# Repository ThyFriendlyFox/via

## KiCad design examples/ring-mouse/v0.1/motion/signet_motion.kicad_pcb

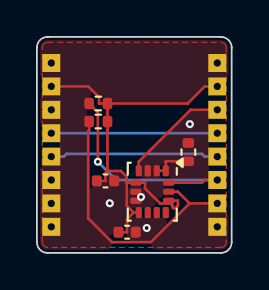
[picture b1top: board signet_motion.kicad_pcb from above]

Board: 2 copper layers, 10.8 x 12.0 mm, 8 parts (0 on the bottom side), 8 nets.

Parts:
C1, C2: 100n; C_0402_1005Metric
J1: POWER; Joint_Edge_1x08_P1.3mm
J2: RADIO; Joint_Edge_1x08_P1.3mm
R1, R2: 4.7k; R_0402_1005Metric
R3: 10k; R_0402_1005Metric
U1: LSM6DSL; LGA-14_3x2.5mm_P0.5mm_LayoutBorder3x4y

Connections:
+3V3: C1.1, C2.1, J1.2, J2.2, R1.2, R2.2, U1.5, U1.8, U1.12
/CHG_STAT: J1.5, J2.5
/I2C_SCL: J2.7, R1.1, U1.13
/I2C_SDA: J2.6, R2.1, U1.14
/IMU_INT: J2.3, U1.4
/IMU_SA0: R3.1, U1.1, U1.2
/VBAT_SENSE: J1.4, J2.4
GND: C1.2, C2.2, J1.1, J1.3, J1.6, J1.7, J1.8, J2.1, J2.8, R3.2, U1.3, U1.6, U1.7

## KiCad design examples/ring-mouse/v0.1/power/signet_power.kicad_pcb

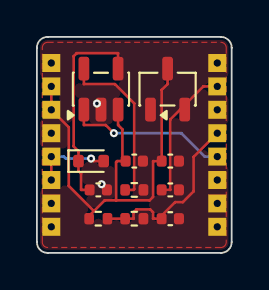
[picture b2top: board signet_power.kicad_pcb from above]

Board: 2 copper layers, 10.8 x 12.0 mm, 13 parts (0 on the bottom side), 8 nets.

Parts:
C1, C2: 4.7u; C_0402_1005Metric
C3, C4: 1u; C_0402_1005Metric
C5: 100n; C_0402_1005Metric
D2: BAT54XV2; D_SOD-523
J1: CELL; Joint_Edge_1x08_P1.3mm
J2: MOTION; Joint_Edge_1x08_P1.3mm
R1: 33k; R_0402_1005Metric
R2, R3: 1M; R_0402_1005Metric
U1: MCP73831; SOT-23-5
U2: TPS7A0533; SOT-23-3

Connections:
+3V3: C4.1, J2.2, U2.2
/CHG_STAT: J2.5, U1.1
/PROG: R1.1, U1.5
/VBAT_SENSE: C5.1, J2.4, R2.2, R3.1
GND: C1.2, C2.2, C3.2, C4.2, C5.2, J1.1, J1.4, J1.7, J1.8, J2.1, J2.3, J2.6, J2.7, J2.8, R1.2, R3.2, U1.2, U2.1
VBAT: C2.1, C3.1, J1.2, J1.3, R2.1, U1.3, U2.3
VCHG: D2.2, J1.5, J1.6
VIN_CHG: C1.1, D2.1, U1.4

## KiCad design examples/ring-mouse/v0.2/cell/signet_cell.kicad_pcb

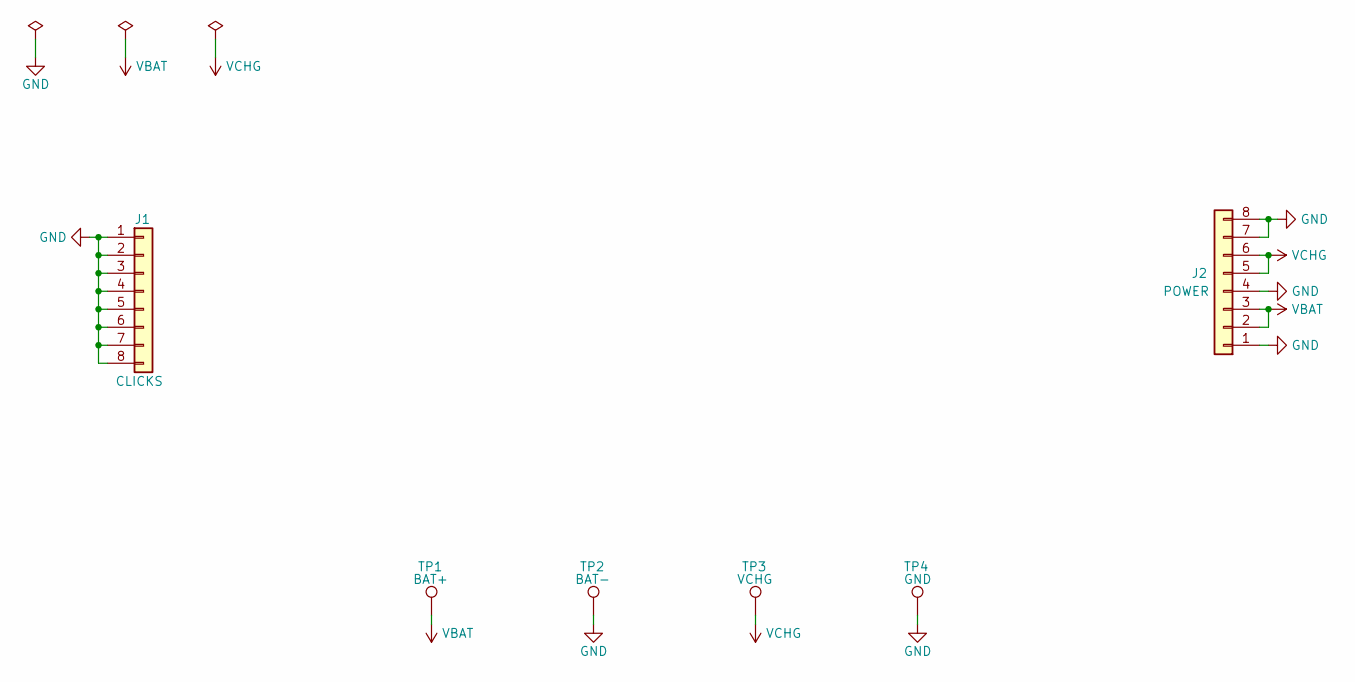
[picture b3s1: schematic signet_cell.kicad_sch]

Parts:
J1: CLICKS; Joint_Edge_1x08_P1.3mm
J2: POWER; Joint_Edge_1x08_P1.3mm
TP1: BAT+; TestPoint_Pad_1.5x1.5mm
TP2: BAT-; TestPoint_Pad_1.5x1.5mm
TP3: VCHG; TestPoint_Pad_D2.0mm
TP4: GND; TestPoint_Pad_D2.0mm

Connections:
GND: J1.1, J1.2, J1.3, J1.4, J1.5, J1.6, J1.7, J1.8, J2.1, J2.4, J2.7, J2.8, TP2.1, TP4.1
VBAT: J2.2, J2.3, TP1.1
VCHG: J2.5, J2.6, TP3.1

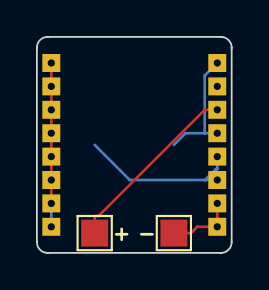
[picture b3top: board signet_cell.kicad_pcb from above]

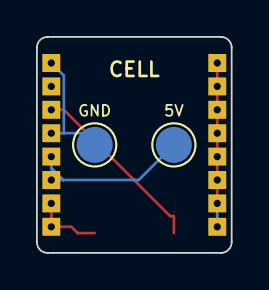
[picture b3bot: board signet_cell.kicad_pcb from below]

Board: 4 copper layers, 10.8 x 12.0 mm, 6 parts (2 on the bottom side), 3 nets.

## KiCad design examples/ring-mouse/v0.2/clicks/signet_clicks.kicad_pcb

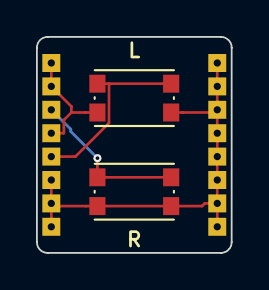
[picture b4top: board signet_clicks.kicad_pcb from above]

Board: 4 copper layers, 10.8 x 12.0 mm, 4 parts (0 on the bottom side), 3 nets.

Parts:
J1: TOUCH; Joint_Edge_1x08_P1.3mm
J2: CELL; Joint_Edge_1x08_P1.3mm
SW1: LEFT; SW_Push_1P1T_NO_CK_KMR2
SW2: RIGHT; SW_Push_1P1T_NO_CK_KMR2

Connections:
/BTN_L: J1.5, SW1.1
/BTN_R: J1.3, SW2.1
GND: J1.1, J1.2, J1.4, J1.6, J1.7, J1.8, J2.1, J2.2, J2.3, J2.4, J2.5, J2.6, J2.7, J2.8, SW1.2, SW2.2

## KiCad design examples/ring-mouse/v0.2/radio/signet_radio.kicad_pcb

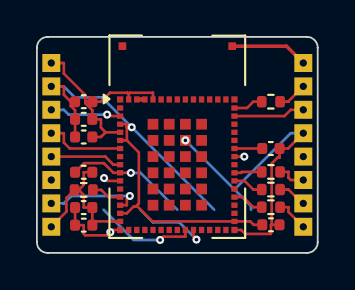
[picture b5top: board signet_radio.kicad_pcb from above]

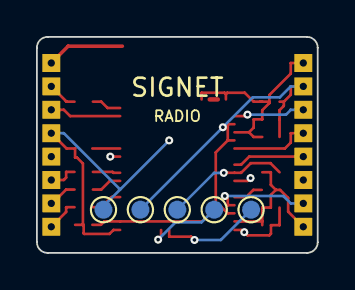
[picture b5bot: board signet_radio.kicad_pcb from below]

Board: 4 copper layers, 15.6 x 12.0 mm, 21 parts (5 on the bottom side), 23 nets.

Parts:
C1: 4.7u; C_0402_1005Metric
C2, C3, C4, C5, C6, C8: 100n; C_0402_1005Metric
C7: 10n; C_0402_1005Metric
J1: MOTION; Joint_Edge_1x08_P1.3mm
J2: TOUCH; Joint_Edge_1x08_P1.3mm
R1, R3, R4, R5: 10k; R_0402_1005Metric
R2: 1k; R_0402_1005Metric
TP1: SWDIO; TestPoint_Pad_D1.0mm
TP2: SWCLK; TestPoint_Pad_D1.0mm
TP3: NRST; TestPoint_Pad_D1.0mm
TP4: 3V3; TestPoint_Pad_D1.0mm
TP5: GND; TestPoint_Pad_D1.0mm
U1: STM32WB5MMG; ST-SiP-LGA-86-11x7.3mm

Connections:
+3V3: C1.1, C2.1, C3.1, C5.1, C6.1, C8.1, J1.2, TP4.1, U1.4, U1.6, U1.15, U1.17, U1.32
/BOOT0: R1.1, U1.13
/BTN_L: J2.5, U1.40
/BTN_R: J2.3, U1.45
/CHG_STAT: J1.5, U1.9
/I2C_SCL: J1.7, U1.14
/I2C_SDA: J1.6, U1.11
/IMU_INT: J1.3, U1.3
/LED: R2.1, U1.46
/LED_A: J2.2, R2.2
/NRST: C4.1, TP3.1, U1.10
/RF: U1.58, U1.59
/SWCLK: TP2.1, U1.26
/SWDIO: TP1.1, U1.25
/TOUCH_A: J2.8, R5.2
/TOUCH_B: J2.7, R4.2
/TOUCH_C: J2.6, R3.2
/TSC_A: R5.1, U1.35
/TSC_B: R4.1, U1.37
/TSC_C: R3.1, U1.38
/TSC_CS: C7.1, U1.41
/VBAT_SENSE: J1.4, U1.7
GND: C1.2, C2.2, C3.2, C4.2, C5.2, C6.2, C7.2, C8.2, J1.1, J1.8, J2.1, J2.4, R1.2, TP5.1, U1.5, U1.16, U1.31, U1.57, U1.60, U1.84, U1.86
